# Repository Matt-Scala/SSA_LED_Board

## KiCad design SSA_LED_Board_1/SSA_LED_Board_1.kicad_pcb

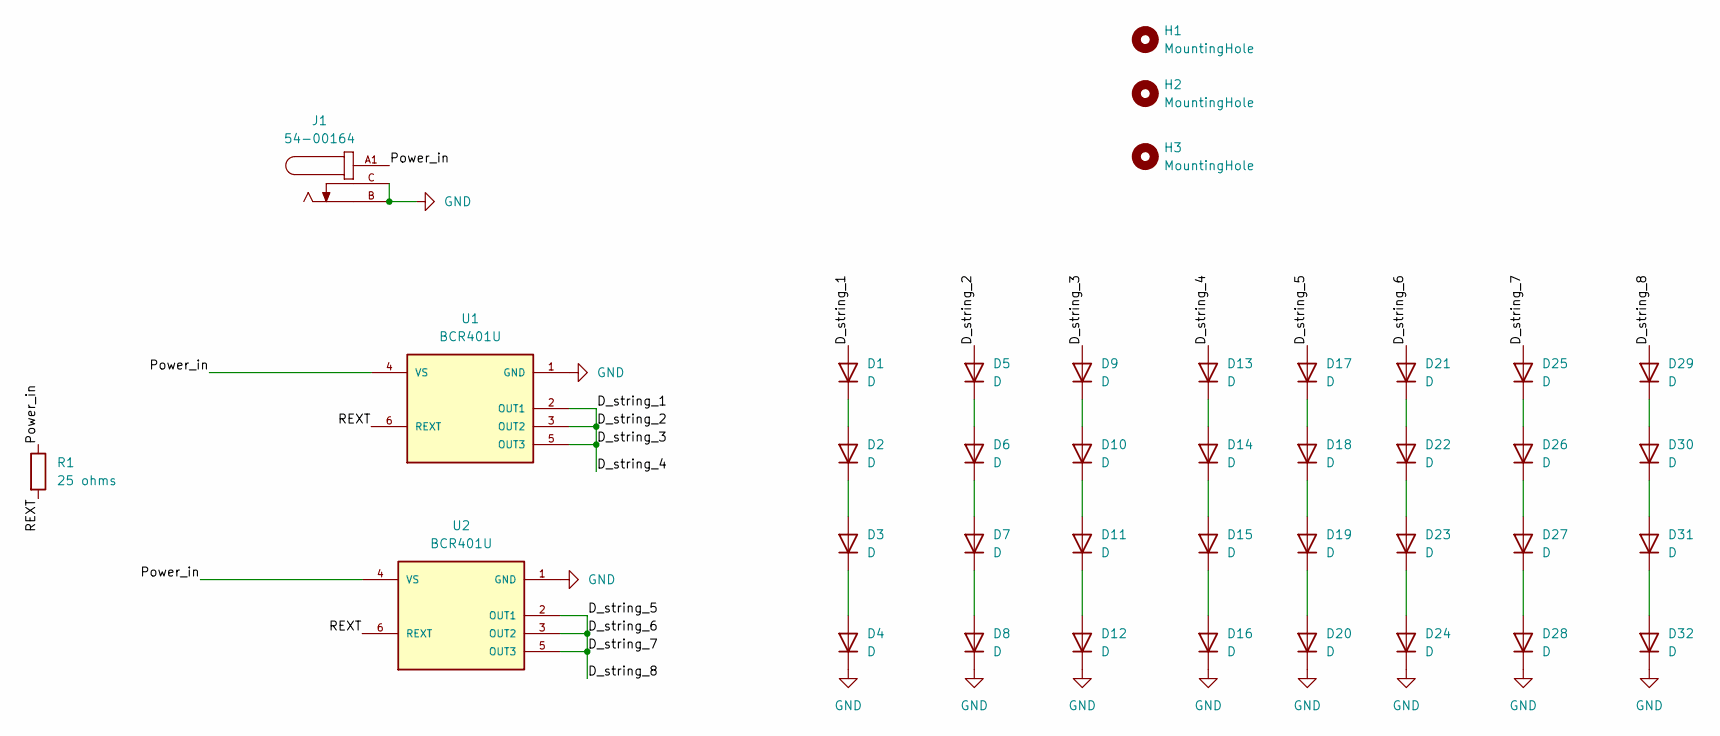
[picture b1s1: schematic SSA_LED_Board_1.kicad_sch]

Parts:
D1, D2, D3, D4, D5, D6, D7, D8, D9, D10, D11, D12, D13, D14, D15, D16, D17, D18, D19, D20, D21, D22, D23, D24, D25, D26, D27, D28, D29, D30, D31, D32: D; D_0603_1608Metric
H1, H2, H3: MountingHole; MountingHole_2.2mm_M2
J1: 54-00164; TENSILITY_54-00164; PARTREV A; DigiKey_Part_Number 839-54-00164CT-ND
R1: 25 ohms; R_0603_1608Metric
U1, U2: BCR401U; SOP95P250X110-6N-1

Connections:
/D_string_1: D1.2 (A), D5.2 (A), D9.2 (A), D13.2 (A), U1.2 (OUT1), U1.3 (OUT2), U1.5 (OUT3)
/D_string_5: D17.2 (A), D21.2 (A), D25.2 (A), D29.2 (A), U2.2 (OUT1), U2.3 (OUT2), U2.5 (OUT3)
/Power_in: J1.A1, J1.A2, R1.1, U1.4 (VS), U2.4 (VS)
/REXT: R1.2, U1.6 (REXT), U2.6 (REXT)
GND: D4.1 (K), D8.1 (K), D12.1 (K), D16.1 (K), D20.1 (K), D24.1 (K), D28.1 (K), D32.1 (K), J1.B, J1.C, U1.1 (GND), U2.1 (GND)
unnamed: D1.1 (K), D2.2 (A)
unnamed: D2.1 (K), D3.2 (A)
unnamed: D3.1 (K), D4.2 (A)
unnamed: D5.1 (K), D6.2 (A)
unnamed: D6.1 (K), D7.2 (A)
unnamed: D7.1 (K), D8.2 (A)
unnamed: D9.1 (K), D10.2 (A)
unnamed: D10.1 (K), D11.2 (A)
unnamed: D11.1 (K), D12.2 (A)
unnamed: D13.1 (K), D14.2 (A)
unnamed: D14.1 (K), D15.2 (A)
unnamed: D15.1 (K), D16.2 (A)
unnamed: D17.1 (K), D18.2 (A)
unnamed: D18.1 (K), D19.2 (A)
unnamed: D19.1 (K), D20.2 (A)
unnamed: D21.1 (K), D22.2 (A)
unnamed: D22.1 (K), D23.2 (A)
unnamed: D23.1 (K), D24.2 (A)
unnamed: D25.1 (K), D26.2 (A)
unnamed: D26.1 (K), D27.2 (A)
unnamed: D27.1 (K), D28.2 (A)
unnamed: D29.1 (K), D30.2 (A)
unnamed: D30.1 (K), D31.2 (A)
unnamed: D31.1 (K), D32.2 (A)

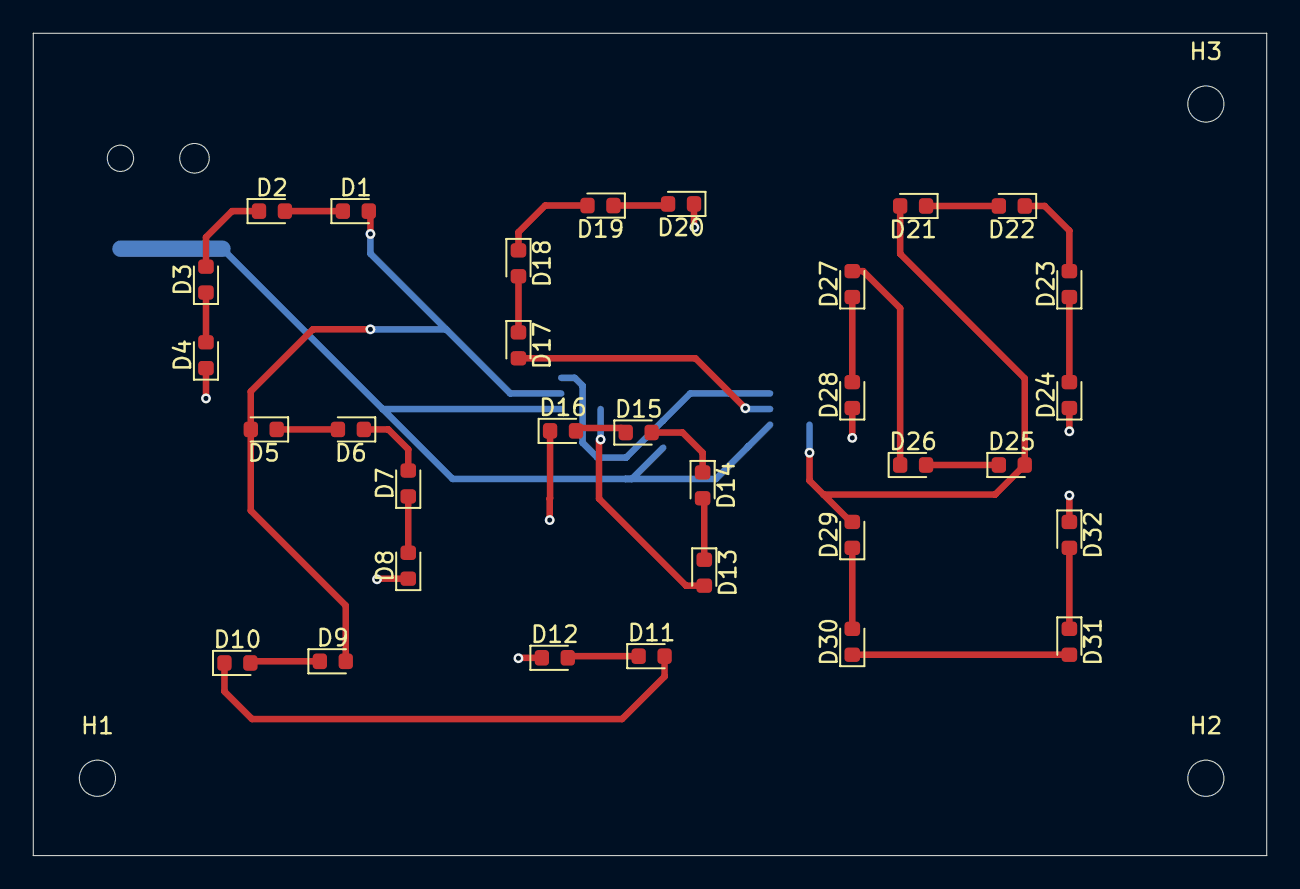
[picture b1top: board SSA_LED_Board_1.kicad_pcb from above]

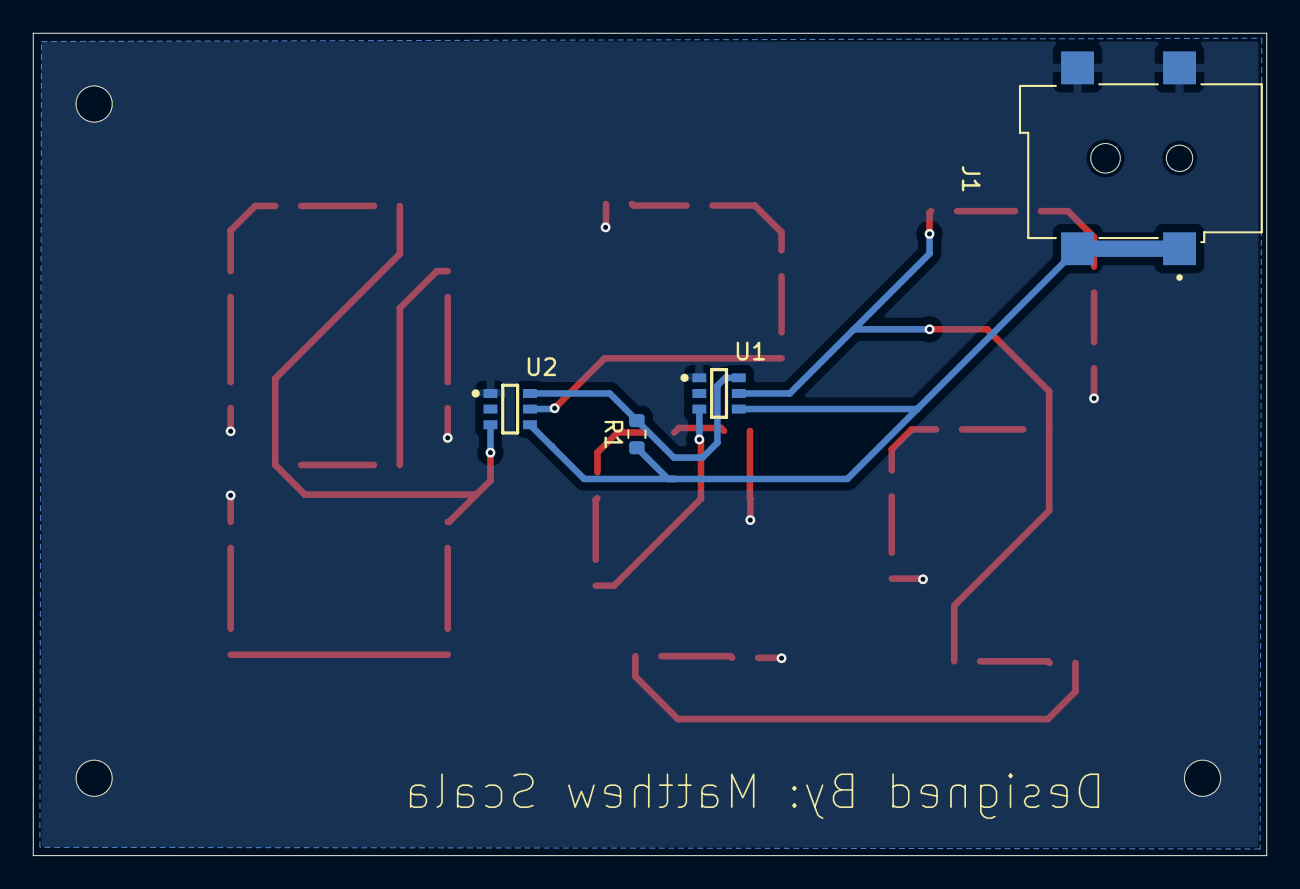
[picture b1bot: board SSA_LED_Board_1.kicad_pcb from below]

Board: 2 copper layers, 75.0 x 50.0 mm, 39 parts (4 on the bottom side), 29 nets.

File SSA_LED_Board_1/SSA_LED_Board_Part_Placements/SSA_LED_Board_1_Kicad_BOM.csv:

"Reference","Qty","Value","DNP","Exclude from BOM","Exclude from Board","Footprint","Datasheet"
"D1,D2,D3,D4,D5,D6,D7,D8,D9,D10,D11,D12,D13,D14,D15,D16,D17,D18,D19,D20,D21,D22,D23,D24,D25,D26,D27,D28,D29,D30,D31,D32","32","D","","","","Diode_SMD:D_0603_1608Metric","~"
"H1,H2,H3,H4","4","MountingHole","","Excluded from BOM","","MountingHole:MountingHole_2.2mm_M2","~"
"J1","1","EJ508A","","","","EJ508A:MPD_EJ508A",""
"R1","1","25 ohms","","","","Resistor_SMD:R_0603_1608Metric","~"
"U1,U2","2","BCR401U","","","","BCR401U:SOP95P250X110-6N-1",""

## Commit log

2026-03-11 initial commit with finished schematic
2026-03-11 finished layout
2026-03-11 Final completed board file
    Still needs a quick DV
